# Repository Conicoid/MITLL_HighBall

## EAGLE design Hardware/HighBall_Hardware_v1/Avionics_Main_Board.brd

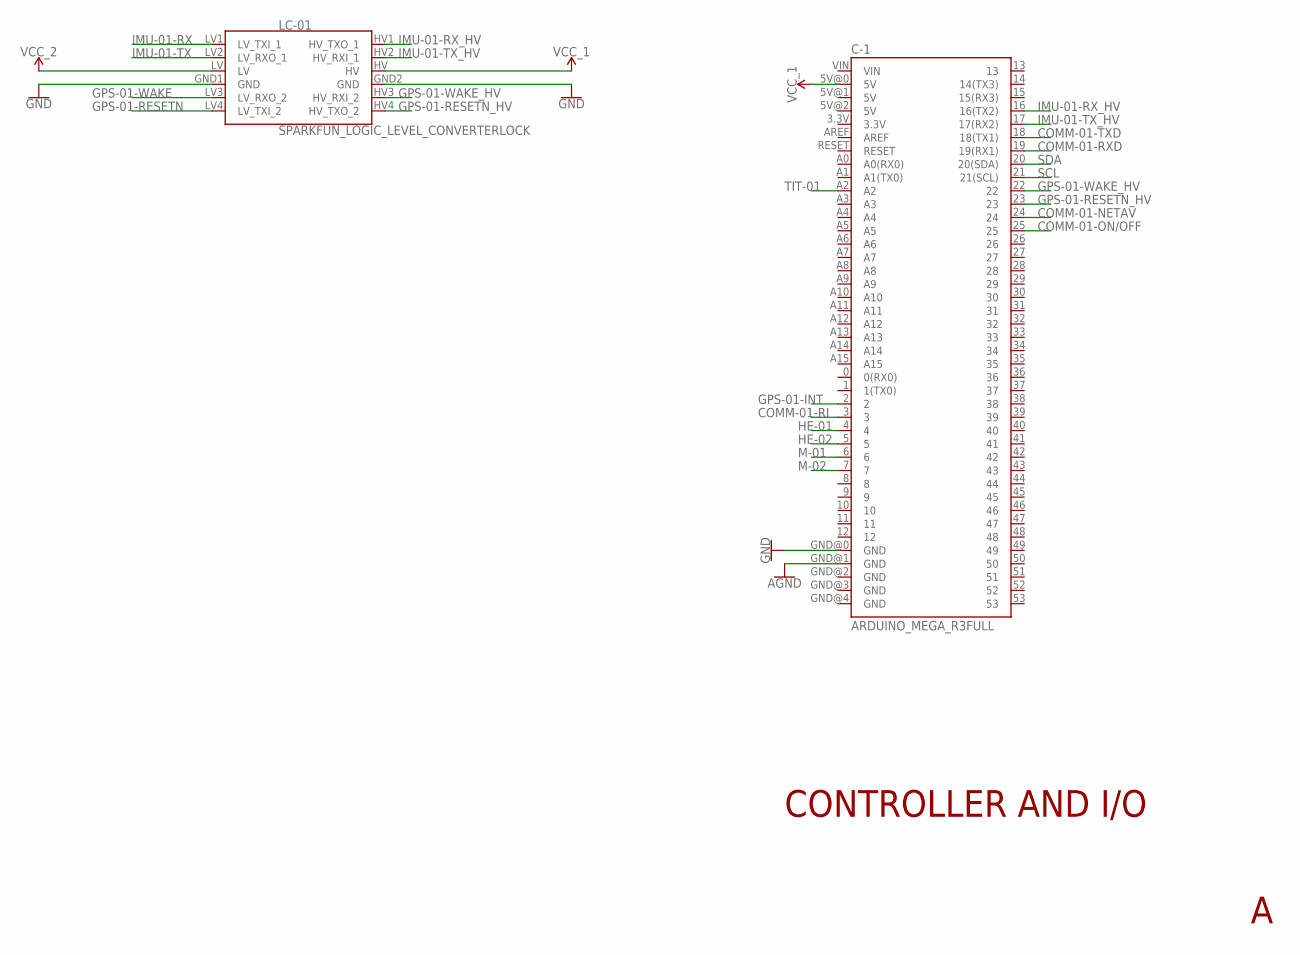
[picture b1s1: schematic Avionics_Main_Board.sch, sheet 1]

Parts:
C-1: ARDUINO_MEGA_R3FULL; ARDUINO_MEGA
LC-01: SPARKFUN_LOGIC_LEVEL_CONVERTERLOCK; SPARKFUN_LOGIC_LEVEL_CONVERTER_LOCK

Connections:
AGND: C-1.GND@1 (GND); also elsewhere on the board
COMM-01-NETAV: C-1.24; also elsewhere on the board
COMM-01-ON/OFF: C-1.25; also elsewhere on the board
COMM-01-RI: C-1.3; also elsewhere on the board
COMM-01-RXD: C-1.19 (19(RX1)); also elsewhere on the board
COMM-01-TXD: C-1.18 (18(TX1)); also elsewhere on the board
GND: C-1.GND@0 (GND), LC-01.GND1 (GND), LC-01.GND2 (GND); also elsewhere on the board
GPS-01-INT: C-1.2; also elsewhere on the board
GPS-01-RESETN: LC-01.LV4 (LV_TXI_2); also elsewhere on the board
GPS-01-RESETN_HV: C-1.23, LC-01.HV4 (HV_TXO_2)
GPS-01-WAKE: LC-01.LV3 (LV_RXO_2); also elsewhere on the board
GPS-01-WAKE_HV: C-1.22, LC-01.HV3 (HV_RXI_2)
HE-01: C-1.4; also elsewhere on the board
HE-02: C-1.5; also elsewhere on the board
IMU-01-RX: LC-01.LV1 (LV_TXI_1); also elsewhere on the board
IMU-01-RX_HV: C-1.16 (16(TX2)), LC-01.HV1 (HV_TXO_1)
IMU-01-TX: LC-01.LV2 (LV_RXO_1); also elsewhere on the board
IMU-01-TX_HV: C-1.17 (17(RX2)), LC-01.HV2 (HV_RXI_1)
M-01: C-1.6; also elsewhere on the board
M-02: C-1.7; also elsewhere on the board
SCL: C-1.21 (21(SCL)); also elsewhere on the board
SDA: C-1.20 (20(SDA)); also elsewhere on the board
TIT-01: C-1.A2; also elsewhere on the board
VCC_1: C-1.5V@0 (5V), LC-01.HV; also elsewhere on the board
VCC_2: LC-01.LV; also elsewhere on the board

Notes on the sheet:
CONTROLLER AND I/O

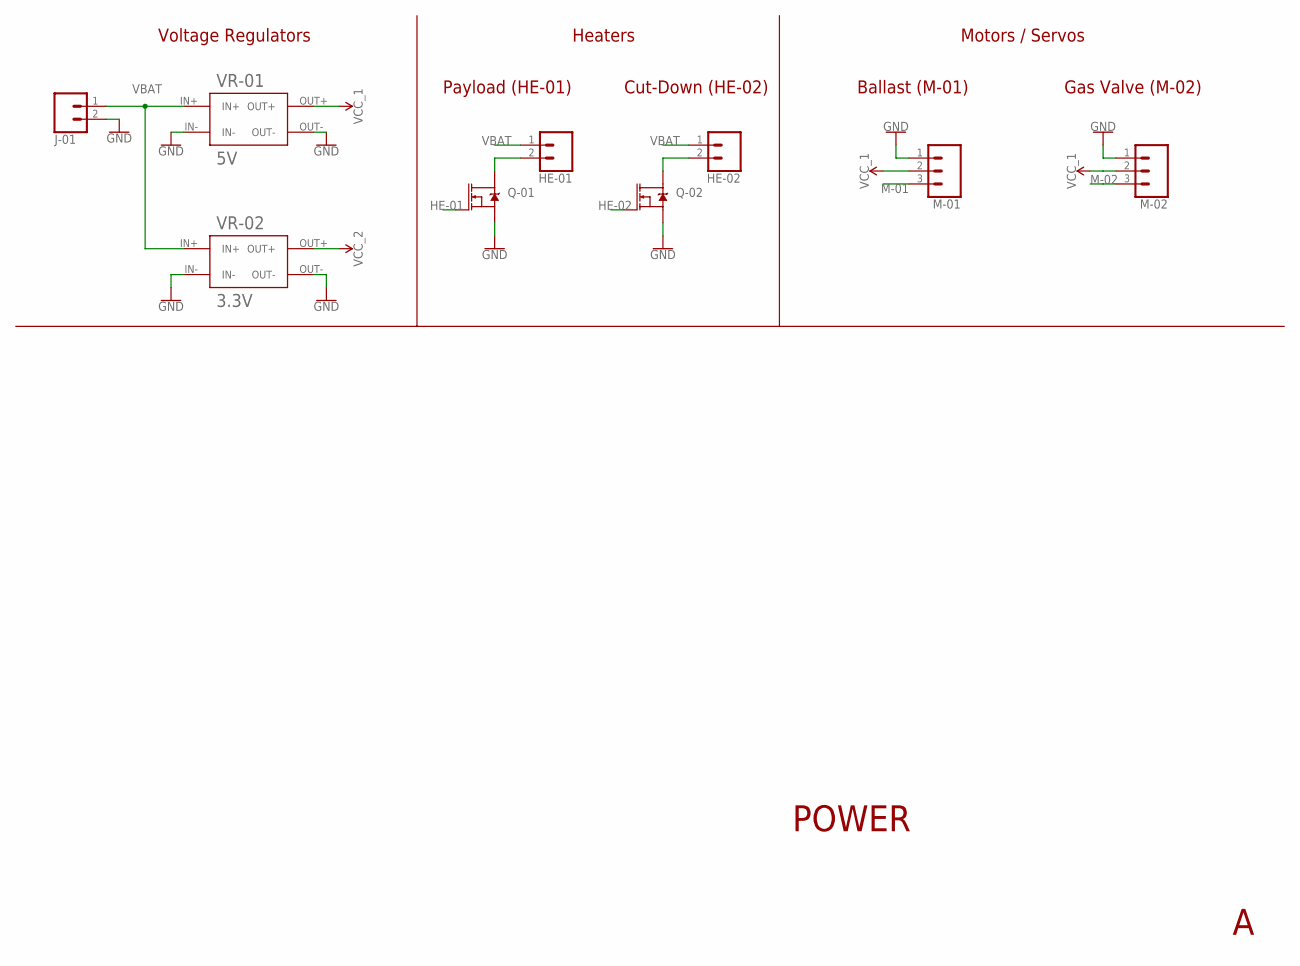
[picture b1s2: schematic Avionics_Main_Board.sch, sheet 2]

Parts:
HE-01, HE-02: CONN_02LOCK; 1X02_LOCK
J-01: CONN_023.5MM_LOCK; SCREWTERMINAL-3.5MM-2_LOCK
M-01, M-02: CONN_03LOCK; 1X03_LOCK
Q-01, Q-02: MOSFET-NCH-FQP30N06L; TO220V
VR-01: 5V; RIORAND_LM2596_BREAKOUT
VR-02: 3.3V; RIORAND_LM2596_BREAKOUT

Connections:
GND: J-01.2, Q-01.3 (S), Q-02.3 (S), VR-01.IN-, VR-01.OUT-, VR-02.IN-, VR-02.OUT-; also elsewhere on the board
HE-01: Q-01.1 (G); also elsewhere on the board
HE-02: Q-02.1 (G); also elsewhere on the board
M-01: M-01.3; also elsewhere on the board
M-02: M-02.3; also elsewhere on the board
unnamed: HE-01.2, Q-01.2 (D)
unnamed: HE-02.2, Q-02.2 (D)
VBAT: HE-01.1, HE-02.1, J-01.1, VR-01.IN+, VR-02.IN+
VCC_1: VR-01.OUT+; also elsewhere on the board
VCC_2: VR-02.OUT+; also elsewhere on the board

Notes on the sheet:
Voltage Regulators
Heaters
Cut-Down (HE-02)
Payload (HE-01)
Motors / Servos
Gas Valve (M-02)
Ballast (M-01)
POWER

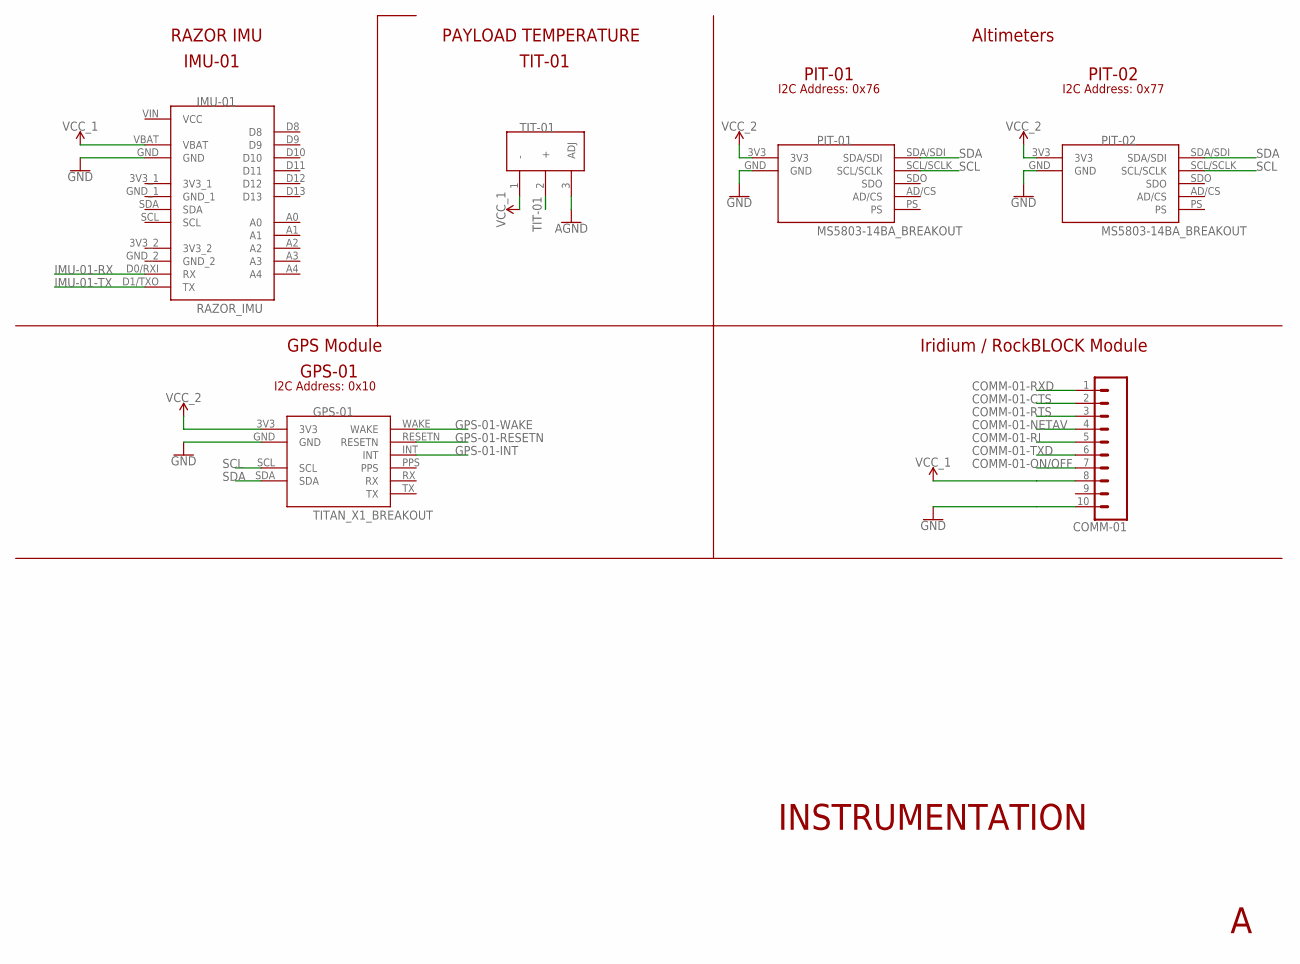
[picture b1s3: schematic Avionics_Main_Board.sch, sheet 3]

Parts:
COMM-01: CONN_10"; 1X10
GPS-01: TITAN_X1_BREAKOUT; QWIIC_TITAN_X1_BREAKOUT
IMU-01: RAZOR_IMU
PIT-01, PIT-02: MS5803-14BA_BREAKOUT
TIT-01: LM335TO-92; TO92

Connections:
AGND: TIT-01.3 (ADJ); also elsewhere on the board
COMM-01-CTS: COMM-01.2
COMM-01-NETAV: COMM-01.4; also elsewhere on the board
COMM-01-ON/OFF: COMM-01.7; also elsewhere on the board
COMM-01-RI: COMM-01.5; also elsewhere on the board
COMM-01-RTS: COMM-01.3
COMM-01-RXD: COMM-01.1; also elsewhere on the board
COMM-01-TXD: COMM-01.6; also elsewhere on the board
GND: COMM-01.10, GPS-01.GND, IMU-01.GND, PIT-01.GND, PIT-02.GND; also elsewhere on the board
GPS-01-INT: GPS-01.INT; also elsewhere on the board
GPS-01-RESETN: GPS-01.RESETN; also elsewhere on the board
GPS-01-WAKE: GPS-01.WAKE; also elsewhere on the board
IMU-01-RX: IMU-01.D0/RXI (RX); also elsewhere on the board
IMU-01-TX: IMU-01.D1/TXO (TX); also elsewhere on the board
SCL: GPS-01.SCL, PIT-01.SCL/SCLK, PIT-02.SCL/SCLK; also elsewhere on the board
SDA: GPS-01.SDA, PIT-01.SDA/SDI, PIT-02.SDA/SDI; also elsewhere on the board
TIT-01: TIT-01.2 (+); also elsewhere on the board
VCC_1: COMM-01.8, IMU-01.VBAT, TIT-01.1 (-); also elsewhere on the board
VCC_2: GPS-01.3V3, PIT-01.3V3, PIT-02.3V3; also elsewhere on the board

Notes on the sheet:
RAZOR IMU
IMU-01
PAYLOAD TEMPERATURE
TIT-01
Altimeters
PIT-01
PIT-02
I2C Address: 0x76
I2C Address: 0x77
GPS Module
GPS-01
I2C Address: 0x10
INSTRUMENTATION
Iridium / RockBLOCK Module

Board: 2 copper layers, 17 parts (1 on the bottom side), 28 nets, no tracks yet.

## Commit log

2018-06-18 Added existing code to git
2018-07-14 Initial Rev of Board and Library Files
2018-07-14 Fixed battery connector
2018-07-16 Avionics Schematic version A
2018-07-16 Added RockBLOCK to schematic
2018-07-18 Setup source files for control payload

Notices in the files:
parts and their libraries:
SparkFun-Boards: Licensing: Creative Commons ShareAlike 4.0 International - https://creativecommons.org/licenses/by-sa/4.0
